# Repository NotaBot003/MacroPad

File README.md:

# HackPad

This is a 12 key macropad with standard mx switchs and one LED per key

## Features
12 keys
16 LEDs
Keyboard Matrix

## CAD Model

Uses m3 bolts and heat set inserts to attach the PCB to the acual case.
3 parts of the case, seprely printed, the bottom, the PCB protector and the lid.

## PCB
Made with KiCad 

## BOM
- 12 Cherry MX Switches
- 12 1U DSA Keycaps
- 12 1N4148 DO-35 Diodes
- 7 M3x5x4 Heatset inserts
- 16 SK6812 MINI-E LEDs
- 1x XIAO RP2040
- 3D printed parts
- A PCB

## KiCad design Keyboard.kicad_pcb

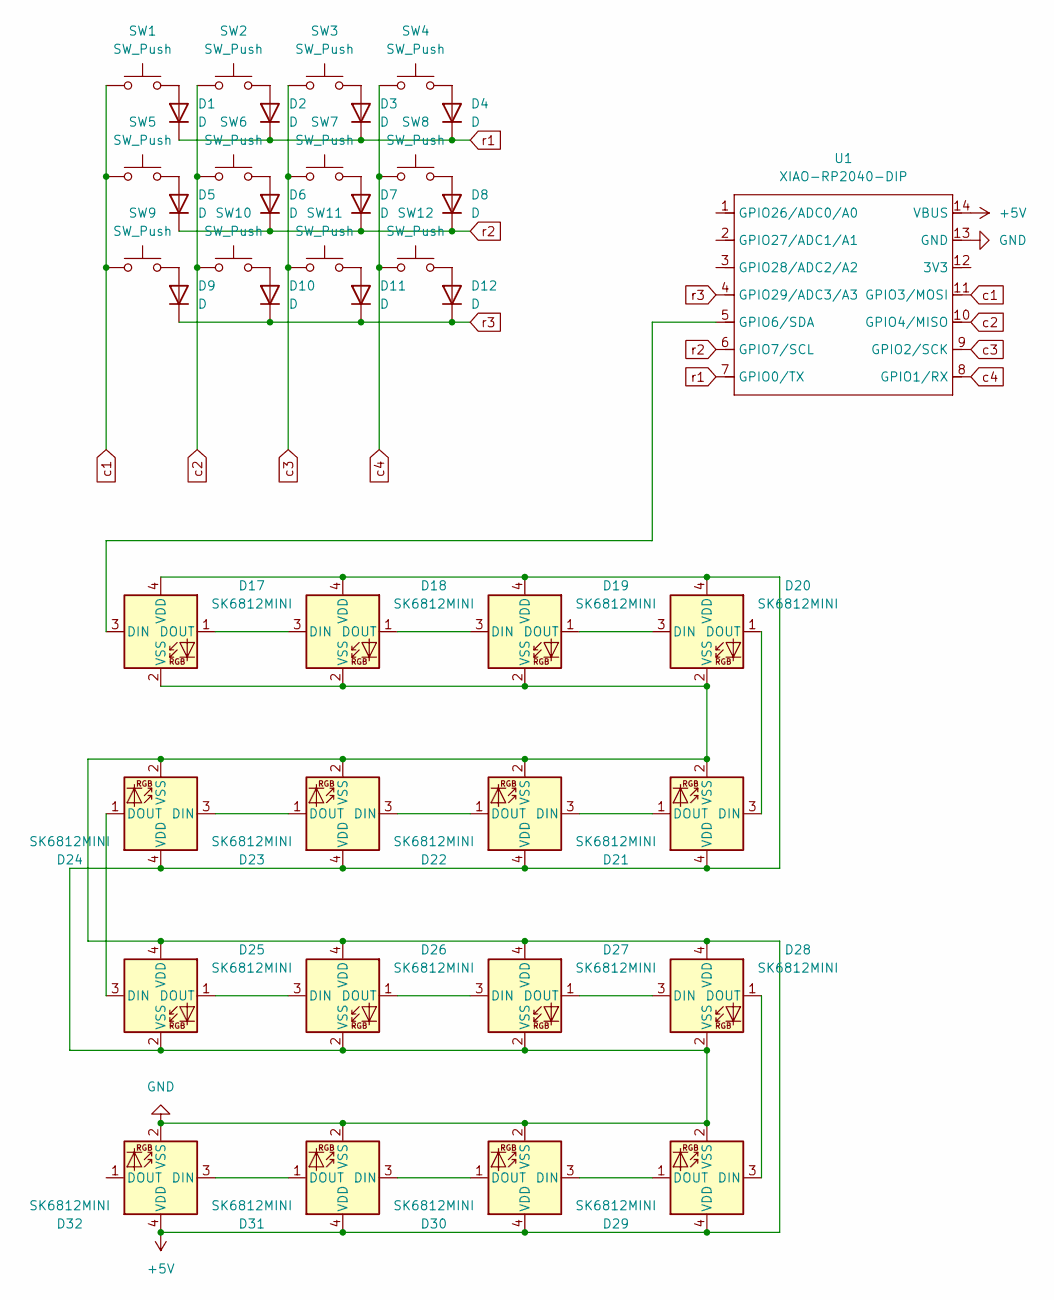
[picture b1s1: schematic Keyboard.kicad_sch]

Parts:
D1, D2, D3, D4, D5, D6, D7, D8, D9, D10, D11, D12: D; D_A-405_P7.62mm_Horizontal
D17, D18, D19, D20, D21, D22, D23, D24, D25, D26, D27, D28, D29, D30, D31, D32: SK6812MINI; LED_SK6812MINI_PLCC4_3.5x3.5mm_P1.75mm
SW1, SW2, SW3, SW4, SW5, SW6, SW7, SW8, SW9, SW10, SW11, SW12: SW_Push; MX_PCB_1.00u
U1: XIAO-RP2040-DIP

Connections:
+5V: D17.2 (VSS), D18.2 (VSS), D19.2 (VSS), D20.2 (VSS), D21.2 (VSS), D22.2 (VSS), D23.2 (VSS), D24.2 (VSS), D25.4 (VDD), D26.4 (VDD), D27.4 (VDD), D28.4 (VDD), D29.4 (VDD), D30.4 (VDD), D31.4 (VDD), D32.4 (VDD), U1.14 (VBUS)
GND: D17.4 (VDD), D18.4 (VDD), D19.4 (VDD), D20.4 (VDD), D21.4 (VDD), D22.4 (VDD), D23.4 (VDD), D24.4 (VDD), D25.2 (VSS), D26.2 (VSS), D27.2 (VSS), D28.2 (VSS), D29.2 (VSS), D30.2 (VSS), D31.2 (VSS), D32.2 (VSS), U1.13 (GND)
unnamed: D1.2 (A), SW1.2
unnamed: D2.2 (A), SW2.2
unnamed: D3.2 (A), SW3.2
unnamed: D4.2 (A), SW4.2
unnamed: D5.2 (A), SW5.2
unnamed: D6.2 (A), SW6.2
unnamed: D7.2 (A), SW7.2
unnamed: D8.2 (A), SW8.2
unnamed: D9.2 (A), SW9.2
unnamed: D10.2 (A), SW10.2
unnamed: D11.2 (A), SW11.2
unnamed: D12.2 (A), SW12.2
unnamed: D17.3 (DIN), U1.5 (GPIO6/SDA)
unnamed: D17.1 (DOUT), D18.3 (DIN)
unnamed: D18.1 (DOUT), D19.3 (DIN)
unnamed: D19.1 (DOUT), D20.3 (DIN)
unnamed: D20.1 (DOUT), D21.3 (DIN)
unnamed: D21.1 (DOUT), D22.3 (DIN)
unnamed: D22.1 (DOUT), D23.3 (DIN)
unnamed: D23.1 (DOUT), D24.3 (DIN)
unnamed: D24.1 (DOUT), D25.3 (DIN)
unnamed: D25.1 (DOUT), D26.3 (DIN)
unnamed: D26.1 (DOUT), D27.3 (DIN)
unnamed: D27.1 (DOUT), D28.3 (DIN)
unnamed: D28.1 (DOUT), D29.3 (DIN)
unnamed: D29.1 (DOUT), D30.3 (DIN)
unnamed: D30.1 (DOUT), D31.3 (DIN)
unnamed: D31.1 (DOUT), D32.3 (DIN)
c1: SW1.1, SW5.1, SW9.1, U1.11 (GPIO3/MOSI)
c2: SW2.1, SW6.1, SW10.1, U1.10 (GPIO4/MISO)
c3: SW3.1, SW7.1, SW11.1, U1.9 (GPIO2/SCK)
c4: SW4.1, SW8.1, SW12.1, U1.8 (GPIO1/RX)
r1: D1.1 (K), D2.1 (K), D3.1 (K), D4.1 (K), U1.7 (GPIO0/TX)
r2: D5.1 (K), D6.1 (K), D7.1 (K), D8.1 (K), U1.6 (GPIO7/SCL)
r3: D9.1 (K), D10.1 (K), D11.1 (K), D12.1 (K), U1.4 (GPIO29/ADC3/A3)

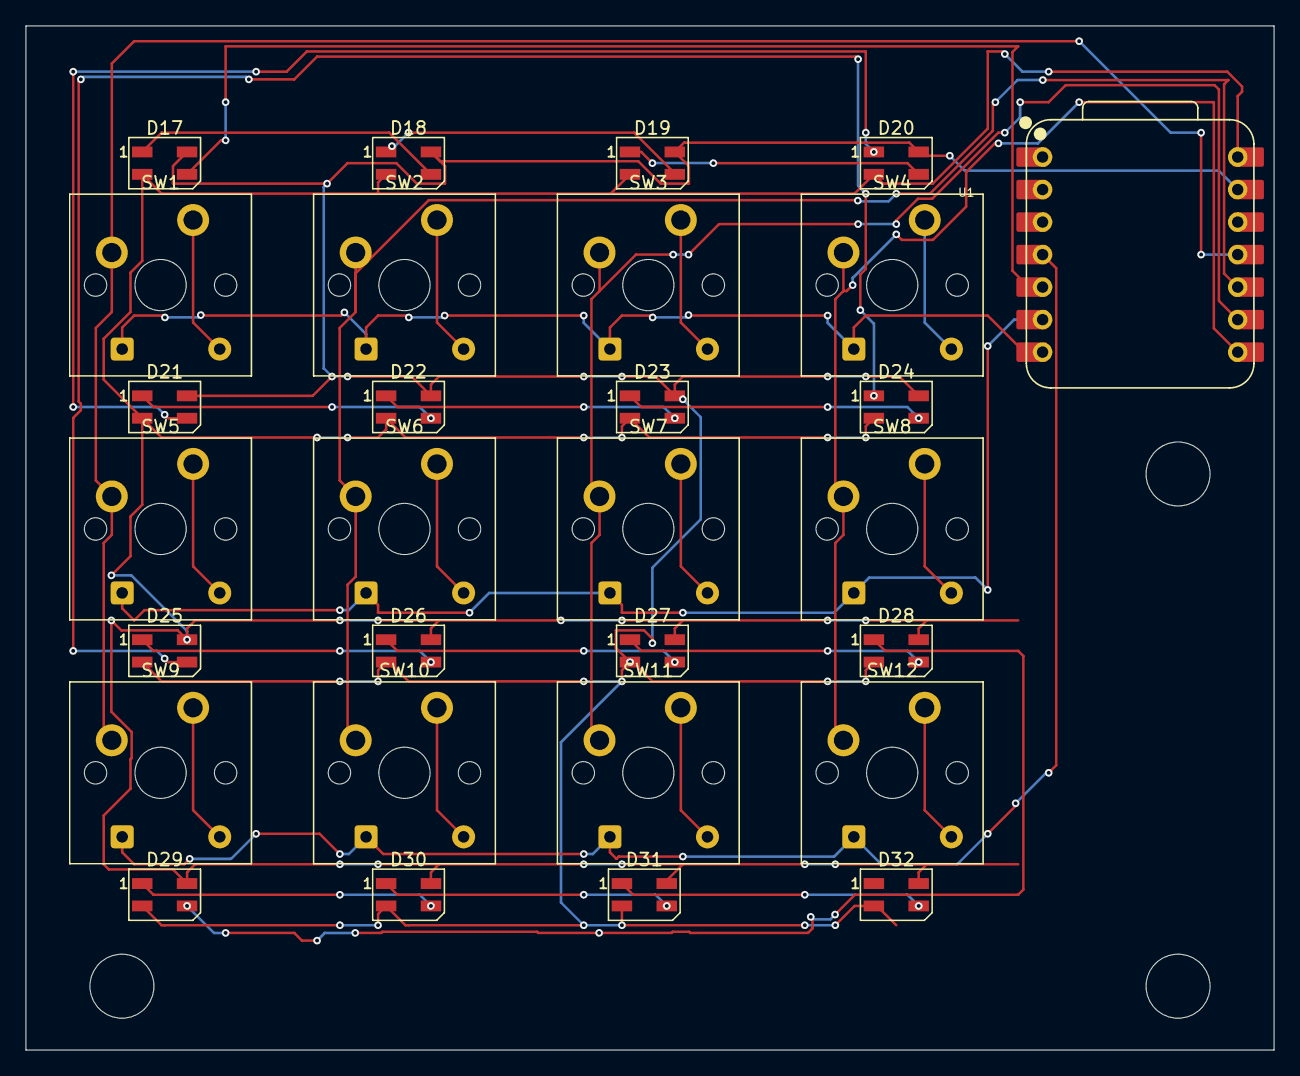
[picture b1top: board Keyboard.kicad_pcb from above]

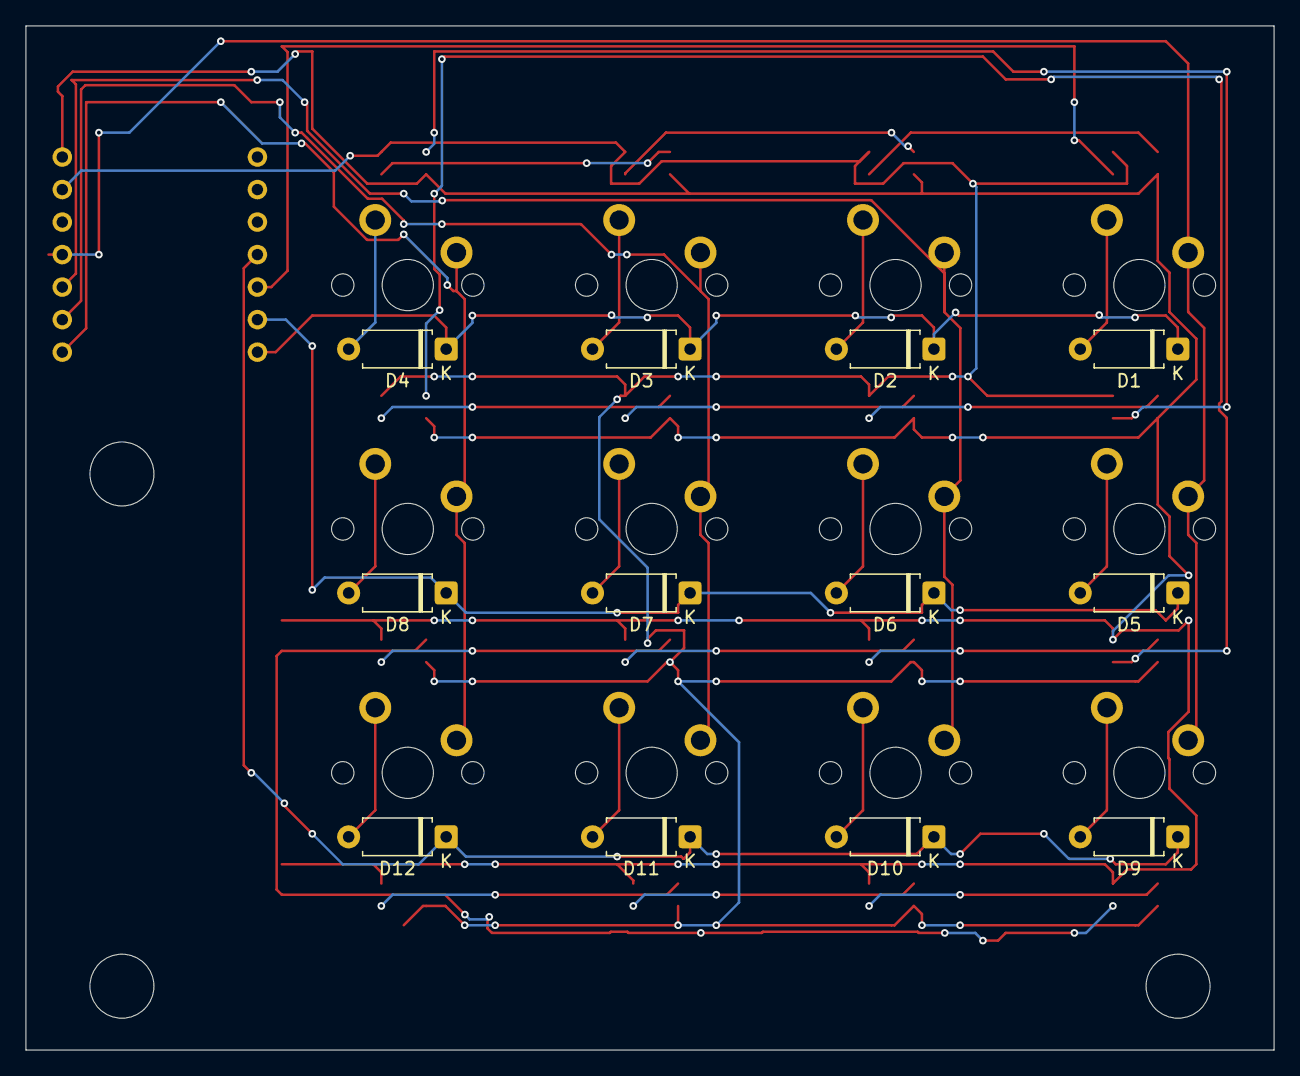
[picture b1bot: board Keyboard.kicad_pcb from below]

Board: 2 copper layers, 97.5 x 80.0 mm, 41 parts (12 on the bottom side), 37 nets.

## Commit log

2025-11-27 Macropad PCBs
2025-11-27 Macropad Case
2025-11-27 Revert "Macropad PCBs"
    This reverts commit f56605794de0c5b79a36c1a2f6ff673fc4321273.
2025-11-27 Revert "Macropad Case"
    This reverts commit 63be3f359646794e27f6c937c626b169485a7815.
2025-11-28 Revert "Add files via upload"
    This reverts commit 8797083649deea1daaf77950df4abe25b6b04e74.
2025-11-28 Macropad
2025-11-29 Revert "Macropad"
    This reverts commit 4aa07dd9c181d186fe5dbc31c9d751c5878f9997.
2025-11-29 Create README.md for HackPad project
    Added detailed information about the HackPad, including features, CAD model, PCB details, and BOM.
2025-11-29 Add images to CAD Model section
    Added images to the CAD Model section of the README.
